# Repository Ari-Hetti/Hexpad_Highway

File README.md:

# Hexpad_Highway
A small macropad with 6  switches, 1 rotary encoder and 1 oled display encased in a 3d printed case

# Contact
@Ari H. U08QRTADZTJ

# BOM
| Component | Qty |  
|-----------|-----|  
| Seeed Xiao RP2040 | 1x |
| MX-Style switches | 6x |  
| Blank DSA keycaps | 6x |
| SK6812 MINI-E LEDs | 6x |    
| EC11 Rotary encoders | 1x |  
| 0.91 inch OLED display | 1x |  
| M3x16mm screws (0.91') | 4x|
| M3x5mx4mm heatset inserts | 4x |  
| PCB | 1x |
| Case | 1x |

# Pictures
| Schematic | PCB | 3D Front | 3D Back | Assemble CAD |  
|------------------|--------------------|-------------|-------| --------|
|  |  |  |  |  |

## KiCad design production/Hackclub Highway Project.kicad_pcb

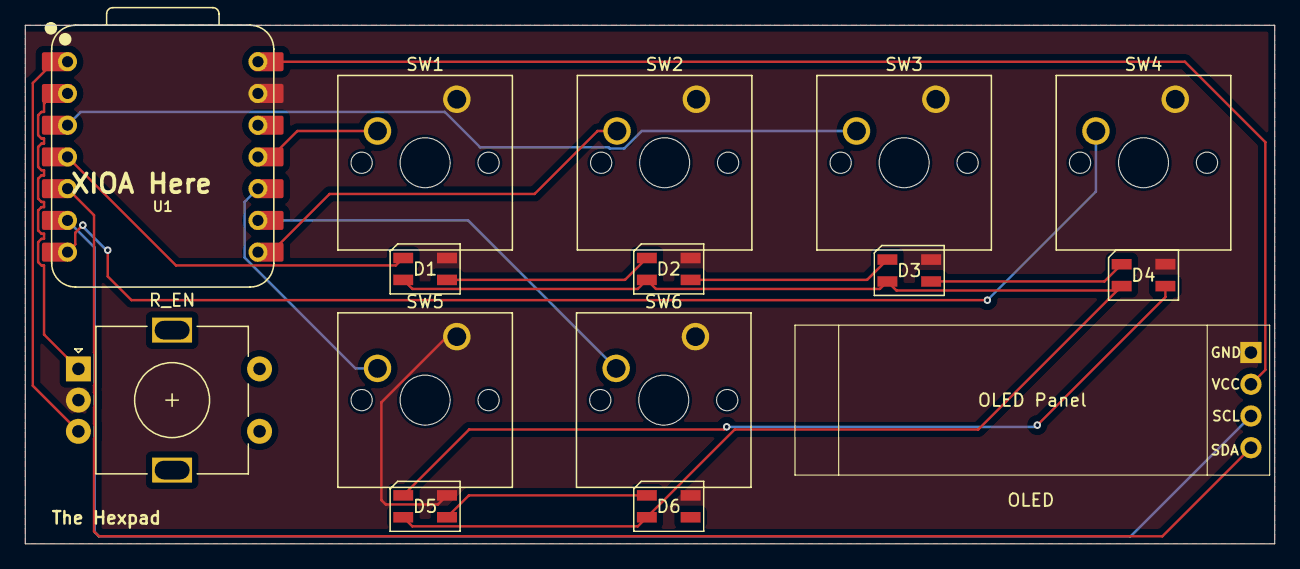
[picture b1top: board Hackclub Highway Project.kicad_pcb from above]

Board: 2 copper layers, 100.0 x 41.5 mm, 15 parts (0 on the bottom side), 19 nets.

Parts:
D1, D2, D3, D4, D5, D6: SK6812MINI; LED_SK6812MINI_PLCC4_3.5x3.5mm_P1.75mm
OLED: OLED_128x32; SSD1306-0.91-OLED-4pin-128x32
R_EN: RotaryEncoder_Switch; RotaryEncoder_Alps_EC11E-Switch_Vertical_H20mm
SW1, SW2, SW3, SW4, SW5, SW6: SW_Push; SW_Cherry_MX_1.00u_PCB
U1: XIAO-RP2040-DIP

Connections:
+5V: OLED.2 (VCC), U1.14 (VBUS)
GND: D1.2 (VSS), D2.2 (VSS), D3.2 (VSS), D4.2 (VSS), D5.2 (VSS), D6.2 (VSS), OLED.1 (GND), R_EN.C, SW1.1, SW2.1, SW3.1, SW4.1, SW5.1, SW6.1, U1.13 (GND)
unnamed: D1.3 (DIN), U1.4 (GPIO29/ADC3/A3)
unnamed: D1.1 (DOUT), D2.3 (DIN)
unnamed: D1.4 (VDD), D2.4 (VDD), D3.4 (VDD), D4.4 (VDD), D5.4 (VDD), D6.4 (VDD)
unnamed: D2.1 (DOUT), D3.3 (DIN)
unnamed: D3.1 (DOUT), D4.3 (DIN)
unnamed: D4.1 (DOUT), D5.3 (DIN)
unnamed: D5.1 (DOUT), D6.3 (DIN)
unnamed: OLED.3 (SCL), U1.6 (GPIO7/SCL)
unnamed: OLED.4 (SDA), U1.5 (GPIO6/SDA)
unnamed: SW4.2, U1.7 (GPIO0/TX)
unnamed: SW2.2, U1.8 (GPIO1/RX)
unnamed: SW6.2, U1.9 (GPIO2/SCK)
unnamed: SW1.2, U1.11 (GPIO3/MOSI)
unnamed: SW5.2, U1.10 (GPIO4/MISO)
unnamed: R_EN.B, U1.1 (GPIO26/ADC0/A0)
unnamed: R_EN.A, U1.2 (GPIO27/ADC1/A1)
unnamed: SW3.2, U1.3 (GPIO28/ADC2/A2)

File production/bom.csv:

Designator,Footprint,Quantity,Value,LCSC Part #
"D1, D2, D3, D4, D5, D6",LED_SK6812MINI_PLCC4_3.5x3.5mm_P1.75mm,6,SK6812MINI,
OLED,SSD1306-0.91-OLED-4pin-128x32,1,OLED_128x32,
R_EN,RotaryEncoder_Alps_EC11E-Switch_Vertical_H20mm,1,RotaryEncoder_Switch,
"SW1, SW2, SW3, SW4, SW5, SW6",SW_Cherry_MX_1.00u_PCB,6,SW_Push,
U1,XIAO-RP2040-DIP,1,XIAO-RP2040-DIP,

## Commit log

2025-07-19 Create PCB
2025-07-19 Rename Hackclub Highway Project - Hexpad 3d Back.png to PCB/Hackclub Highway Project - Hexpad 3d Back.png
2025-07-19 Rename Hackclub Highway Project - Hexpad 3d Front.png to PCB/Hackclub Highway Project - Hexpad 3d Front.png
2025-07-19 Rename Hackclub Highway Project - Hexpad PCB.png to PCB/Hackclub Highway Project - Hexpad PCB.png
2025-07-19 Rename Hackclub Highway Project - Hexpad Schematic.png to PCB/Hackclub Highway Project - Hexpad Schematic.png
2025-07-19 Rename Hackclub Highway Project.kicad_pro to PCB/Hackclub Highway Project.kicad_pro
2025-07-19 Rename Hackclub Highway Project.step to PCB/Hackclub Highway Project.step
2025-07-28 Rename Hackclub Highway Project - Hexpad 3d Back Final.png to PCB/Hackclub Highway ProjecHexpad 3d Back Final.png
2025-07-28 Rename Hackclub Highway Project - Hexpad 3d Front Final.png to PCB/Hackclub Highway Project - Hexpad 3d Front Final.png
2025-07-28 Rename Hackclub Highway Project - Hexpad PCB Final.png to PCB/Hackclub Highway Project - Hexpad PCB Final.png
2025-07-28 Rename Hackclub Highway Project - Hexpad Schematic Final.png to PCB/Hackclub Highway Project - Hexpad Schematic Final.png
2025-07-28 Rename Hackclub Highway Project - Hexpad CAD Final.png to CAD/Hackclub Highway Project - Hexpad CAD Final.png
2025-08-05 Rename PCB/Hackclub Highway ProjecHexpad 3d Back Final.png to PCB/Assets/Hackclub Highway ProjecHexpad 3d Back Final.png
2025-08-05 Rename PCB/Hackclub Highway Project - Hexpad 3d Front Final.png to PCB/Assets/Hackclub Highway Project - Hexpad 3d Front Final.png
2025-08-05 Rename PCB/Hackclub Highway Project - Hexpad PCB Final.png to PCB/Assets/Hackclub Highway Project - Hexpad PCB Final.png
2025-08-05 Rename PCB/Hackclub Highway Project - Hexpad Schematic Final.png to PCB/Assets/Hackclub Highway Project - Hexpad Schematic Final.png
2025-08-05 Rename Hackclub Highway Project - Hexpad CAD Final.png to Hackclub Highway Project - Hexpad CAD Final.png
2025-08-05 Rename PCB/Assets/Hackclub Highway ProjecHexpad 3d Back Final.png to Assets/Hackclub Highway ProjecHexpad 3d Back Final.png
2025-08-05 Rename PCB/Assets/Hackclub Highway Project - Hexpad 3d Front Final.png to Assets/Hackclub Highway Project - Hexpad 3d Front Final.png
2025-08-05 Rename PCB/Assets/Hackclub Highway Project - Hexpad PCB Final.png to Assets/Hackclub Highway Project - Hexpad PCB Final.png
2025-08-05 Rename PCB/Assets/Hackclub Highway Project - Hexpad Schematic Final.png to Assets/Hackclub Highway Project - Hexpad Schematic Final.png
2025-08-05 Rename Hackclub Highway Project.kicad_prl to PCB/Hackclub Highway Project.kicad_prl
2025-08-05 Update and rename Hackclub Highway Project.kicad_sch-bak to PCB/Hackclub Highway Project.kicad_sch-bak
2026-01-04 Rename code.py to Firmware/code.py
2026-01-05 Rename Screenshot 2025-12-28 214518.png to Assets/Screenshot 2025-12-28 214518.png
2026-01-05 Rename Screenshot 2025-12-28 214518.png to Hackclub Highway Project - Hexpad Final
2026-01-05 Rename Hackclub Highway Project Hexpad Final Assembly.png to Assets/Hackclub Highway Project Hexpad Final Assembly.png
2026-02-15 Update quantities of screws and inserts in README
